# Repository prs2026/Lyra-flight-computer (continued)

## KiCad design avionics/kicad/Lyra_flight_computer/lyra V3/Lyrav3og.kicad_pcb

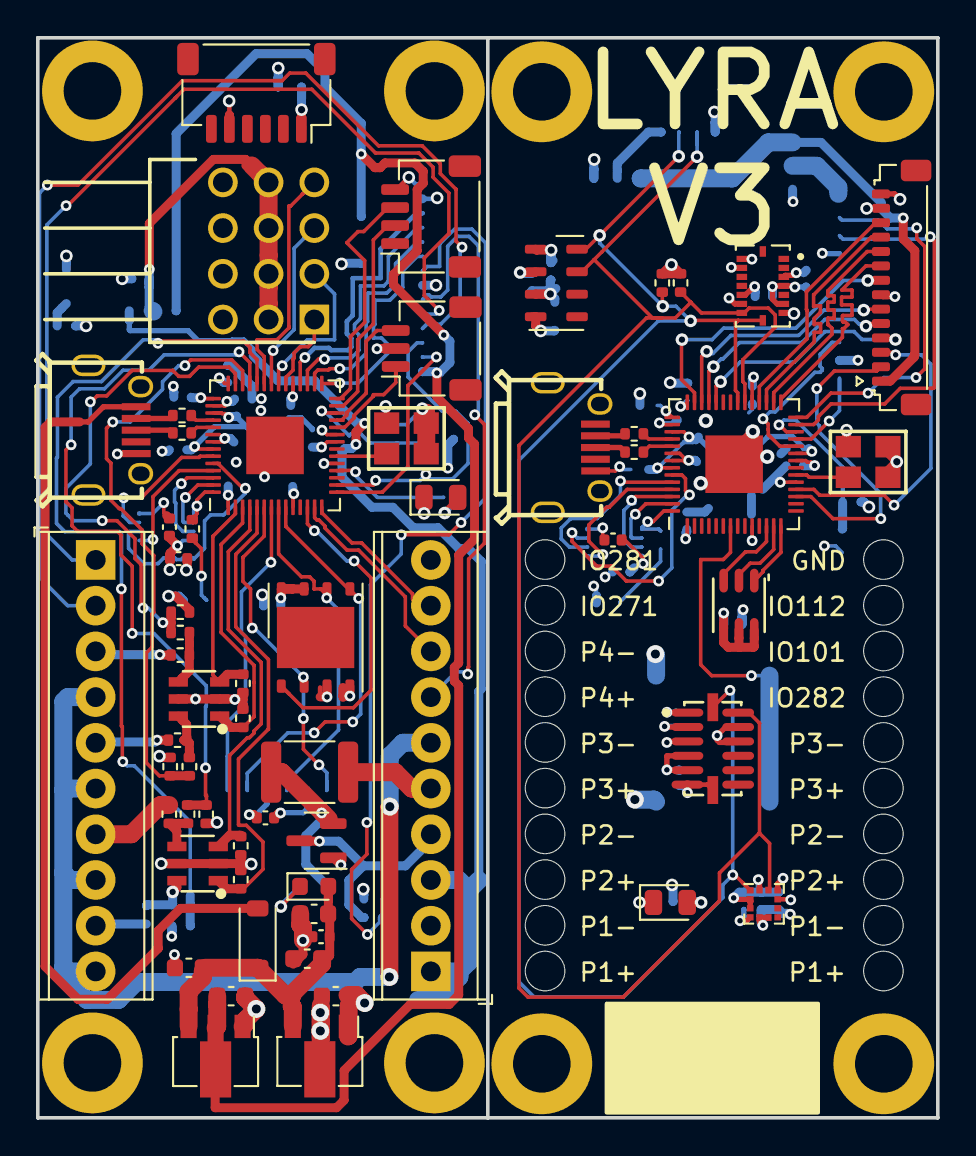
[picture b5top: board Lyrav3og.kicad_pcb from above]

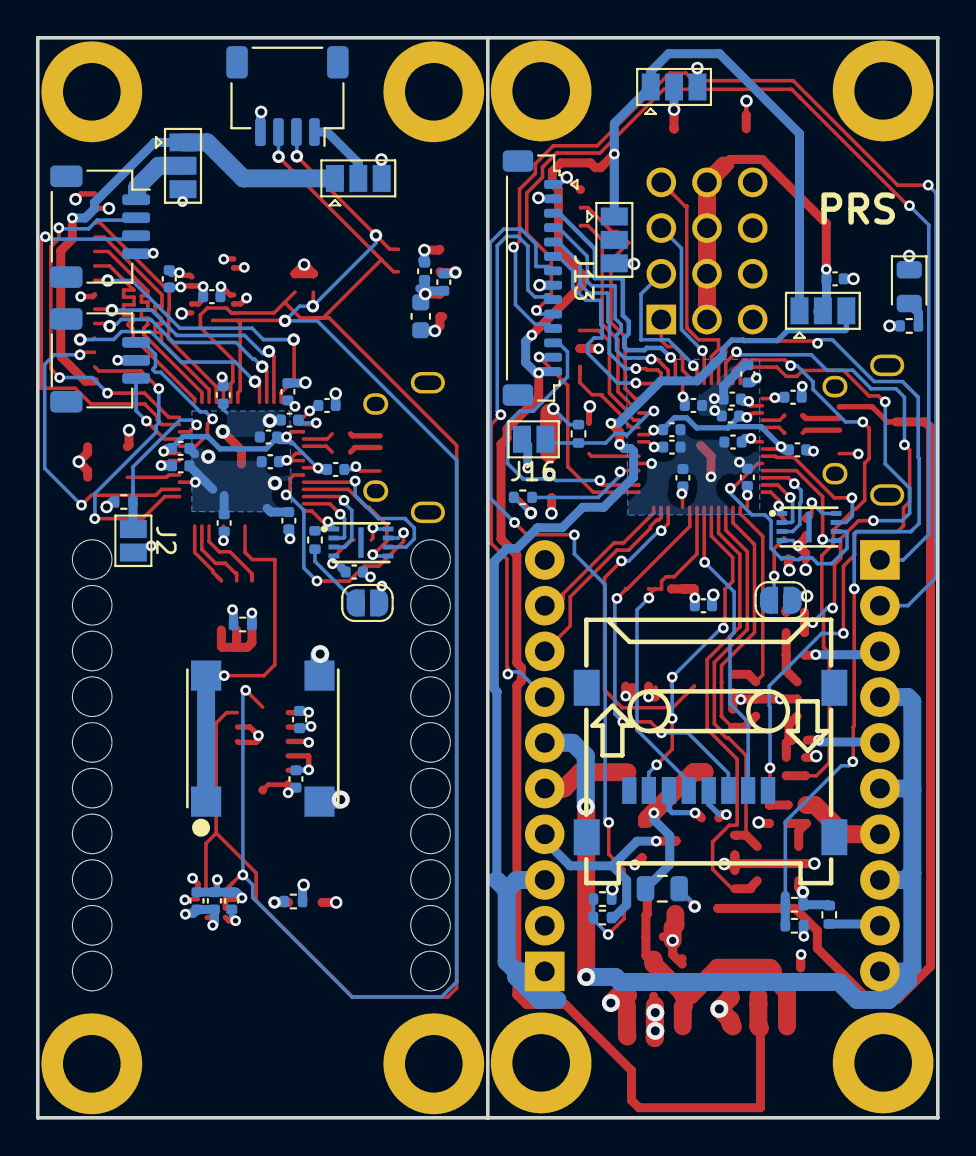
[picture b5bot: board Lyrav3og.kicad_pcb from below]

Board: 4 copper layers, 50.0 x 60.0 mm, 135 parts (66 on the bottom side), 114 nets.

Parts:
BUZZER1: MLT-7525; BUZ-SMD_4P-L7.5-W7.5-P7.59-TL
C1, C6, C7, C8, C9, C13, C15, C17, C19, C20, C21, C24, C25, C26, C27, C28, C29, C30, C32, C35, C38, C39, C40, C41, C42, C43, C44, C46: 100n; C_0402_1005Metric
C2, C3, C4, C5: 22u; C_0603_1608Metric
C10, C11: 10u; C_0603_1608Metric
C12, C14, C16, C22, C23, C33, C34, C36, C37: 1u; C_0402_1005Metric
C31, C45: 2u2; C_0402_1005Metric
Card2: TF-002-H18; SIM-SMD_TF-002-H18
D1: D_Small; D_SOD-123
D2, D3, D4: LED; LED_0805_2012Metric
F1: 2a; Fuse_1812_4532Metric
F2: 200ma; Fuse_0805_2012Metric
FB1: FerriteBead_Small; D_0603_1608Metric
H1, H2, H3, H4, H5, H6, H7, H8: MountingHole_Pad; MountingHole_3.2mm_M3_DIN965_Pad
H9, H10: Access Hole; 1x10 2.54mm pitch acess hole
J1, J3, J5: Conn_01x04; JST_SH_SM04B-SRSS-TB_1x04-1MP_P1.00mm_Horizontal
J2, J16: Conn_01x02; SolderJumper-2_P1.3mm_Open_Pad1.0x1.5mm
J4, J17: Conn_01x03; JST_SH_SM03B-SRSS-TB_1x03-1MP_P1.00mm_Horizontal
J6, J15: USB_B_Micro; MICRO-USB-SMD_U254-051T-4BHJ25-F2S
J7: Conn_02x03_Odd_Even; JST_SH_SM06B-SRSS-TB_1x06-1MP_P1.00mm_Horizontal
J8, J13: Conn_01x14; JST_SUR_SM14B-SURS-TF_1x14-1MP_P0.80mm_Horizontal
J9, J12: Conn_01x02; SolderJumper-2_P1.3mm_Open_RoundedPad1.0x1.5mm
J10: TSW-104-08-T-T-RA; HDRRA12W64P254_3X4_1016X254X810P
J11, J18: Screw_Terminal_01x10; TerminalBlock_Phoenix_MPT-0,5-10-2.54_1x10_P2.54mm_Horizont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
JP1, JP2, JP3, JP4, JP5: SolderJumper_3_Open; SolderJumper-3_P1.3mm_Open_Pad1.0x1.5mm
LED1: FM-Z2727RGBA-SH; LED-SMD_6P-L2.7-W2.8-TL
Q1: AO3401A; SOT-23
Q2, Q3: KY6802; SOT-23-6_L2.9-W1.6-P0.95-LS2.8-BL
R1, R4, R26, R27, R28, R32: 1k; R_0402_1005Metric
R2, R7, R8, R17, R18: 20k; R_0402_1005Metric
R3, R9, R10, R19, R20: 6k; R_0402_1005Metric
R5, R6, R15, R16: 10R; R_0402_1005Metric
R11, R12, R23, R24: 470R; R_0402_1005Metric
R13, R14: 2k2; R_0402_1005Metric
R21, R22, R29, R30: 27R; R_0402_1005Metric
R25, R31: 10k; R_0402_1005Metric
U1: AMS1117-5.0; SOT-89-3
U2: AMS1117-3.3; SOT-89-3
U3: W25Q32JVZP; WSON-8-1EP_6x5mm_P1.27mm_EP3.4x4.3mm
U4: BMI088; PQFN50P450X300X100-16N
U5: MPL3115A2; NXP_LGA-8_3x5mm_P1.25mm_H1.1mm
U6: ADXL375BCCZ-RL7; LGA-14_L5.0-W3.0-P0.80-BL
U7: LIS3MDL; LGA-12_2x2mm_P0.5mm
U8, U10: RP2040; QFN-56-1EP_7x7mm_P0.4mm_EP3.2x3.2mm
U9, U11: W25Q16JVUXIQ; USON-8_L3.0-W2.0-P0.50-BL-EP
X1, X2: S3D12.288000B20F30T; OSC-SMD_4P-L3.2-W2.5-BL_SIT8008BI

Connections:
+1V1: C20.1, C21.1, C22.1, U8.23 (DVDD), U8.45 (VREG_VOUT), U8.50 (DVDD)
+1V2: C6.1, C35.1, C36.1, U10.23 (DVDD), U10.45 (VREG_VOUT), U10.50 (DVDD)
+3V3: C1.1, C5.1, C7.1, C8.1, C9.1, C10.1, C14.1, C15.1, C16.1, C17.1, C23.1, C24.1, C25.1, C26.1, C27.1, C28.1, C29.1, C30.1, C31.1, C32.1, C34.2, C37.1, C38.1, C39.1, C40.1, C41.1, C42.1, C43.1, C44.1, C45.1, C46.1, Card2.4 (VDD), J8.13, J13.2, JP1.3 (B), JP2.3 (B), JP3.3 (B), JP4.3 (B), R1.2, R4.2, R13.1, R14.1, R25.1, R27.2, R31.1, U2.2 (VO), U3.3 (IO2), U3.7 (IO3), U3.8 (VCC), U4.3 (VDD), U4.7 (PS), U4.11 (VDDIO), U4.14 (CSB1), U5.1 (VDD), U5.4 (VDDIO), U6.1 (VDDI/O), U6.3 (RESERVED), U6.6 (VS), U6.7 (~CS), U7.5 (Vdd), U7.6 (Vdd_IO), U7.10 (~CS), U8.1 (IOVDD), U8.10 (IOVDD), U8.22 (IOVDD), U8.33 (IOVDD), U8.42 (IOVDD), U8.43 (ADC_AVDD), U8.44 (VREG_IN), U8.48 (USB_VDD), U8.49 (IOVDD), U9.8 (VCC), U10.1 (IOVDD), U10.10 (IOVDD), U10.22 (IOVDD), U10.33 (IOVDD), U10.42 (IOVDD), U10.43 (ADC_AVDD), U10.44 (VREG_IN), U10.48 (USB_VDD), U10.49 (IOVDD), U11.8 (VCC), X1.1 (Tri-state), X1.4 (VDD), X2.1 (Tri-state), X2.4 (VDD)
+5V: J8.1, JP2.1 (A), JP3.1 (A)
+5VD: C3.1, J13.14, JP1.1 (A), JP4.1 (A), JP5.1 (A), U1.2 (VO)
+12P: F1.2, J18.5
+12V: J18.4, Q1.3 (D), R2.1
+12VA: C2.1, C4.1, C11.1, C12.1, D1.1 (K), FB1.2, U1.3 (VI), U2.3 (VI)
+BATT: J18.1, J18.3, JP5.3 (B)
/ BOT RP USB_D+: R29.2, U10.47 (USB_DP)
/BATT SENSE: J8.8, U8.41 (GPIO29_ADC3)
/BATT SENSE BOT: J13.7, R2.2, R3.1
/BOOTSEL: J9.2, R26.2
/BOOTSEL BOT: J12.2, R32.2
/BOT RP USB_D-: R30.1, U10.46 (USB_DM)
/BOT USB_D+: J15.3 (D+), R29.1
/BOT USB_D-: J15.2 (D-), R30.2
/BRKOUT CS BOT: J7.6, U10.11 (GPIO8)
/BUZZER: BUZZER1.1 (+), BUZZER1.4, U8.7 (GPIO5)
/FLASH CS BOT: U3.1 (~CS), U10.12 (GPIO9)
/GPIO26: J8.4, U8.38 (GPIO26_ADC0)
/GPIO26 BOT: J11.2, J13.11
/GPIO27: J8.5, U8.39 (GPIO27_ADC1)
/GPIO27 BOT: J11.1, J13.10
/GPIO28: J8.6, U8.40 (GPIO28_ADC2)
/GPIO28 BOT: J13.9, J18.7
/GPIO 102 BOT: J18.8, U10.13 (GPIO10)
/GPIO 112 BOT: J18.9, U10.14 (GPIO11)
/I2C1 SCL: J3.2, R13.2, U4.8 (SCL/SCK), U5.8 (SCL), U6.14 (SCL/SCLK), U7.1 (SCL/SPC), U8.35 (GPIO23)
/I2C1 SDA: J3.3, R14.2, U4.9 (SDA/SDI), U5.7 (SDL), U6.13 (SDA/SDI/SDIO), U7.11 (SDA/SDI/SDO), U8.34 (GPIO22)
/I2C PWR: J3.1, JP2.2 (C)
/INT12: J8.3, U8.18 (GPIO15)
/INT12 BOT: J13.12, U10.16 (GPIO13)
/INT21: J8.2, U8.17 (GPIO14)
/INT21 BOT: J13.13, U10.15 (GPIO12)
/LED BOT: R28.2, U10.18 (GPIO15)
/LEDBLUE: LED1.1 (-), U8.14 (GPIO11)
/LEDGREEN: LED1.2 (-), U8.13 (GPIO10)
/LEDRED: LED1.3 (-), U8.12 (GPIO9)
/P1 CONT BOT: R7.2, R9.1, U10.38 (GPIO26_ADC0)
/P1 EN BOT: Q2.1 (G), R11.2, U10.5 (GPIO3)
/P1-: J11.9, R5.1
/P2 CONT BOT: R17.2, R19.1, U10.39 (GPIO27_ADC1)
/P2 EN BOT: Q2.3 (G), R23.2, U10.4 (GPIO2)
/P2-: J11.7, R15.1
/P3 CONT BOT: R8.2, R10.1, U10.40 (GPIO28_ADC2)
/P3 EN BOT: Q3.1 (G), R12.2, U10.3 (GPIO1)
/P3-: J11.5, R6.1
/P4 CONT BOT: R18.2, R20.1, U10.41 (GPIO29_ADC3)
/P4 EN BOT: Q3.3 (G), R24.2, U10.2 (GPIO0)
/P4-: J11.3, R16.1
/PYRO PWR: J11.4, J11.6, J11.8, J11.10, J18.6
/QSPI_SCLK: U8.52 (QSPI_SCLK), U9.6 (CLK)
/QSPI_SCLK BOT: U10.52 (QSPI_SCLK), U11.6 (CLK)
/QSPI_SD1: U8.55 (QSPI_SD1), U9.2 (DO(IO1))
/QSPI_SD1 BOT: U10.55 (QSPI_SD1), U11.2 (DO(IO1))
/QSPI_SD2: U8.54 (QSPI_SD2), U9.3 (WP#(IO2))
/QSPI_SD2 BOT: U10.54 (QSPI_SD2), U11.3 (WP#(IO2))
/QSPI_SD3: U8.51 (QSPI_SD3), U9.7 (HOLD#orRESET#(IO3))
/QSPI_SD3 BOT: U10.51 (QSPI_SD3), U11.7 (HOLD#orRESET#(IO3))
/QSPI_SDO: U8.53 (QSPI_SD0), U9.5 (DI(IO0))
/QSPI_SDO BOT: U10.53 (QSPI_SD0), U11.5 (DI(IO0))
/QSPI_SS: R26.1, U8.56 (QSPI_SS), U9.1 (~CS)
/QSPI_SS BOT: R32.1, U10.56 (QSPI_SS), U11.1 (~CS)
/RP USB_D+: R21.2, U8.47 (USB_DP)
/RP USB_D-: R22.1, U8.46 (USB_DM)
/RUN: J2.1, R25.2, U8.26 (RUN)
/RUN BOT: J16.1, R31.2, U10.26 (RUN)
/SD CS BOT: Card2.2 (CD/DAT3), U10.7 (GPIO5)
/SERVO1: J10.1, U10.34 (GPIO22)
/SERVO2: J10.4, U10.35 (GPIO23)
/SERVO3: J10.7, U10.36 (GPIO24)
/SERVO4: J10.10, U10.37 (GPIO25)
/SERVO PWR: C33.1, J10.2, J10.5, J10.8, J10.11, JP5.2 (C)
/SPI0 CSn: J8.12, U8.32 (GPIO21)
/SPI0 CSn BOT: J13.3, U10.32 (GPIO21)
/SPI0 MISO: J8.10, U8.30 (GPIO19)
/SPI0 MISO BOT: J13.5, U10.30 (GPIO19)
/SPI0 MOSI: J8.11, U8.31 (GPIO20)
/SPI0 MOSI BOT: J13.4, U10.31 (GPIO20)
/SPI0 SCK: J8.9, U8.29 (GPIO18)
/SPI0 SCK BOT: J13.6, U10.29 (GPIO18)
/SPI1 MISO BOT: Card2.7 (DAT0), J7.4, U3.2 (DO(IO1)), U10.6 (GPIO4)
/SPI1 MOSI BOT: Card2.3 (CMD), J7.3, U3.5 (DI(IO0)), U10.9 (GPIO7)
/SPI1 PWR BOT: J7.1, JP4.2 (C)
/SPI1 SCLK BOT: Card2.5 (CLX), J7.2, U3.6 (CLK), U10.8 (GPIO6)
/SWCLK: J4.1, U8.24 (SWCLK)
/SWCLK BOT: J17.1, U10.24 (SWCLK)
/SWD: J4.3, U8.25 (SWD)
/SWD BOT: J17.3, U10.25 (SWD)
/UART0 RX: J5.2, U8.28 (GPIO17)
/UART0 RX BOT: J1.3, U10.28 (GPIO17)
/UART0 TX: J5.3, U8.27 (GPIO16)
/UART0 TX BOT: J1.2, U10.27 (GPIO16)
/UART PWR: J5.1, JP3.2 (C)
/UART PWR BOT: J1.1, JP1.2 (C)
/USB_D+: J6.3 (D+), R21.1
/USB_D-: J6.2 (D-), R22.2
/XIN: U8.20 (XIN), X1.3 (OUTPUT)
/XIN BOT: U10.20 (XIN), X2.3 (OUTPUT)
GND: BUZZER1.2 (-), BUZZER1.3, C1.2, C2.2, C3.2, C4.2, C5.2, C6.2, C7.2, C8.2, C9.2, C10.2, C11.2, C12.2, C13.2, C14.2, C15.2, C16.2, C17.2, C19.2, C20.2, C21.2, C22.2, C23.2, C24.2, C25.2, C26.2, C27.2, C28.2, C29.2, C30.2, C31.2, C32.2, C33.2, C34.1, C35.2, C36.2, C37.2, C38.2, C39.2, C40.2, C41.2, C42.2, C43.2, C44.2, C45.2, C46.2, Card2.6 (VSS), D2.1 (K), D3.1 (K), D4.1 (K), H1.1, H2.1, H3.1, H4.1, H5.1, H6.1, H7.1, H8.1, J1.4, J2.2, J3.4, J4.2, J5.4, J6.5 (GND), J7.5, J8.7, J8.14, J9.1, J10.3, J10.6, J10.9, J10.12, J12.1, J13.1, J13.8, J15.5 (GND), J16.2, J17.2, J18.2, J18.10, Q1.1 (G), Q2.2 (S), Q2.5 (S), Q3.2 (S), Q3.5 (S), R3.2, R9.2, R10.2, R11.1, R12.1, R19.2, R20.2, R23.1, R24.1, U1.1 (GND), U2.1 (GND), U3.4 (GND), U4.4 (GNDA), U4.6 (GNDIO), U4.10 (SDO2), U4.15 (SDO1), U5.3 (GND), U6.2 (GND), U6.4 (GND), U6.5 (GND), U6.11 (RESERVED), U6.12 (SDO/ALTADDRESS), U7.2 (GND), U7.3 (GND), U7.9 (SDO/SA1), U7.12 (GND), U8.19 (TESTEN), U8.57 (GND), U9.4 (GND), U10.19 (TESTEN), U10.57 (GND), U11.4 (GND), X1.2 (GND), X2.2 (GND)
unnamed: D2.2 (A), R1.1
unnamed: D3.2 (A), R27.1
unnamed: D4.2 (A), R28.1
unnamed: F2.2, FB1.1
unnamed: LED1.4 (+), LED1.5 (+), LED1.6 (+), R4.1
unnamed: F1.1, F2.1, Q1.2 (S)
unnamed: Q2.6 (D), R5.2, R7.1
unnamed: Q2.4 (D), R15.2, R17.1
unnamed: Q3.6 (D), R6.2, R8.1
unnamed: Q3.4 (D), R16.2, R18.1
unnamed: C13.1, U5.2 (CAP)
unnamed: C19.1, U7.4 (C1)
VBUS: D1.2 (A), J15.1 (VBUS)
